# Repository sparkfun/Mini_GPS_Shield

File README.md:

# Pro_Mini_GPS_Shield
A GPS Shield for the Arduino Pro Mini

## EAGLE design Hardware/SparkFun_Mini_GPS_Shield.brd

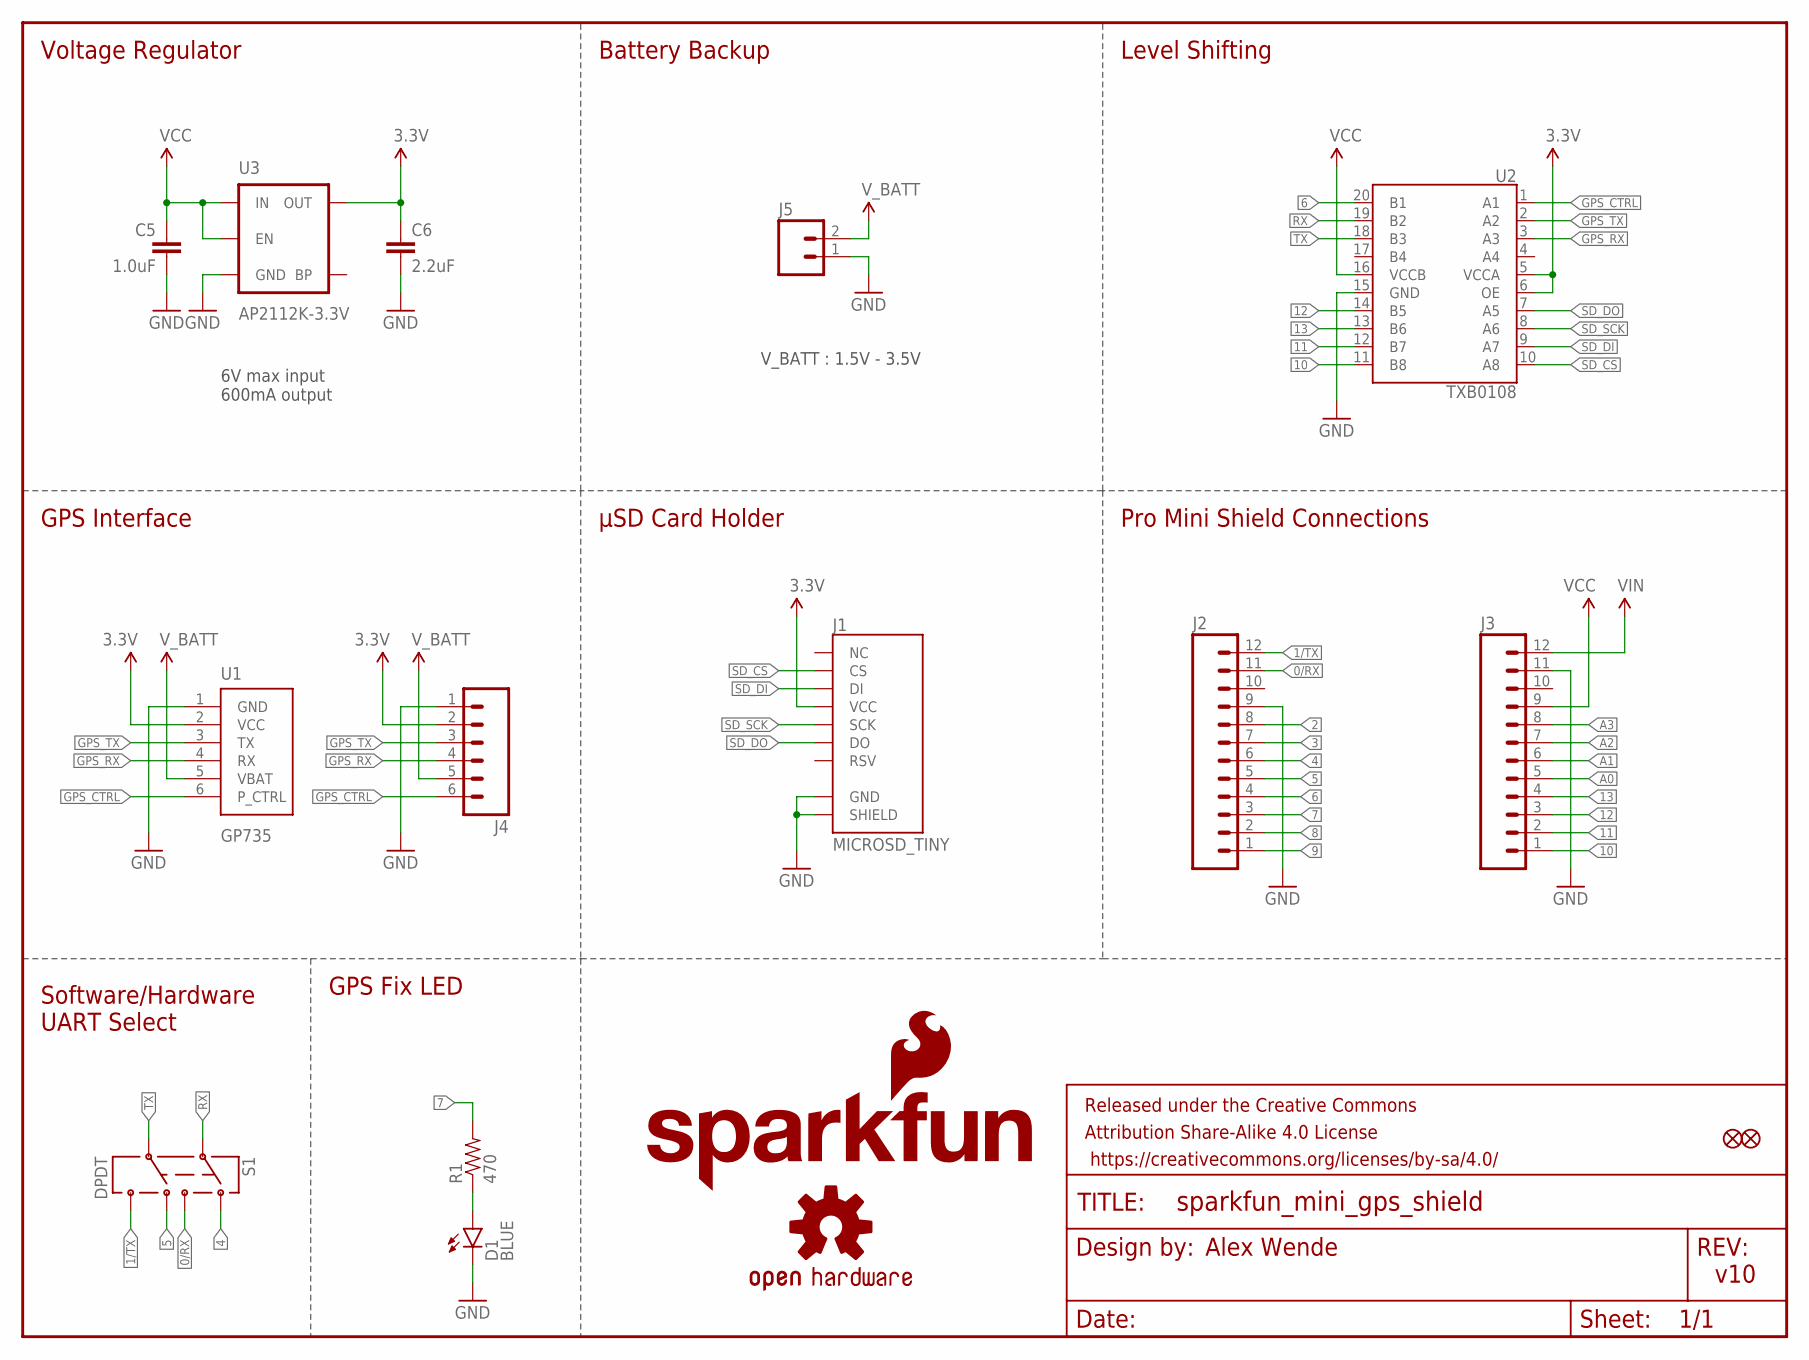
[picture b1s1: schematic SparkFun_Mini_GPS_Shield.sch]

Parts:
C5: 1.0uF; 0805-CAP
C6: 2.2uF; 0603-CAP
D1: BLUE; LED-0603
FD1, FD2: FIDUCIALUFIDUCIAL; MICRO-FIDUCIAL
FRAME1: FRAME-LETTER; CREATIVE_COMMONS
J1: MICROSD_TINY
J2, J3: M12NO_SILK; 1X12_NO_SILK
J4: M06NO_SILK_FEMALE_PTH; 1X06_NO_SILK
J5: M021X02_NO_SILK; 1X02_NO_SILK
LOGO1: OSHW-LOGOS; OSHW-LOGO-S
LOGO3: SFE_LOGO_FLAME.1_INCH; SFE_LOGO_FLAME_.1
LOGO4: SFE_LOGO_NAME.1_INCH; SFE_LOGO_NAME_.1
R1: 470; 0603-RES
S1: DPDT; AYZ0202
U1: GP735
U2: TXB0108; UFDFN-20
U3: AP2112K-3.3V; SOT23-5

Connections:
0/RX: J2.11, S1.3
1/TX: J2.12, S1.6
2: J2.8
3: J2.7
3.3V: C6.1, J1.4 (VCC), J4.2, U1.2 (VCC), U2.5 (VCCA), U2.6 (OE), U3.5 (OUT)
4: J2.6, S1.1
5: J2.5, S1.4
6: J2.4, U2.20 (B1)
7: J2.3, R1.2
8: J2.2
9: J2.1
10: J3.1, U2.11 (B8)
11: J3.2, U2.12 (B7)
12: J3.3, U2.14 (B5)
13: J3.4, U2.13 (B6)
A0: J3.5
A1: J3.6
A2: J3.7
A3: J3.8
GND: C5.2, C6.2, D1.C, J1.6 (GND), J1.GND1 (SHIELD), J1.GND2 (SHIELD), J1.GND3 (SHIELD), J1.GND4 (SHIELD), J1.GND5 (SHIELD), J1.GND6 (SHIELD), J2.9, J3.11, J4.1, J5.1, U1.1 (GND), U2.15 (GND), U3.2 (GND)
GPS_CTRL: J4.6, U1.6 (P_CTRL), U2.1 (A1)
GPS_RX: J4.4, U1.4 (RX), U2.3 (A3)
GPS_TX: J4.3, U1.3 (TX), U2.2 (A2)
unnamed: D1.A, R1.1
RX: S1.2, U2.19 (B2)
SD_CS: J1.2 (CS), U2.10 (A8)
SD_DI: J1.3 (DI), U2.9 (A7)
SD_DO: J1.7 (DO), U2.7 (A5)
SD_SCK: J1.5 (SCK), U2.8 (A6)
TX: S1.5, U2.18 (B3)
VCC: C5.1, J3.9, U2.16 (VCCB), U3.1 (IN), U3.3 (EN)
VIN: J3.12
V_BATT: J4.5, J5.2, U1.5 (VBAT)

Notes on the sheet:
6V max input 600mA output
Voltage Regulator
Battery Backup
Level Shifting
GPS Interface
Pro Mini Shield Connections
μSD Card Holder
Software/Hardware UART Select
GPS Fix LED
Alex Wende
v10
V_BATT : 1.5V - 3.5V

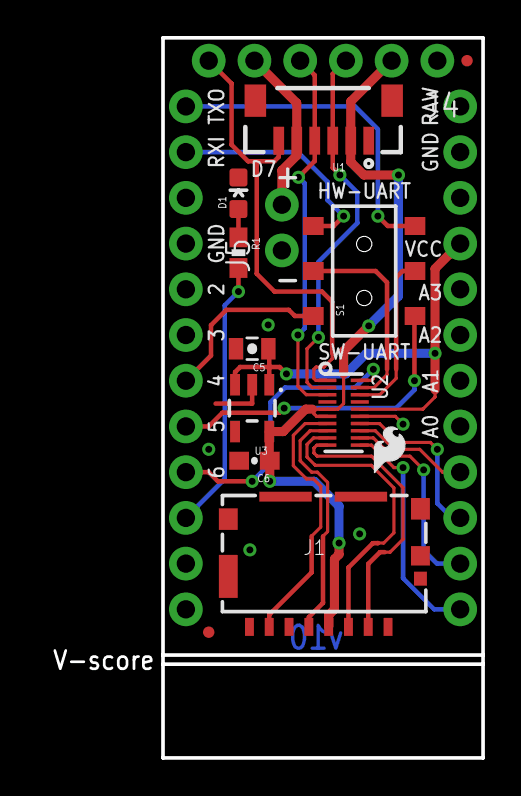
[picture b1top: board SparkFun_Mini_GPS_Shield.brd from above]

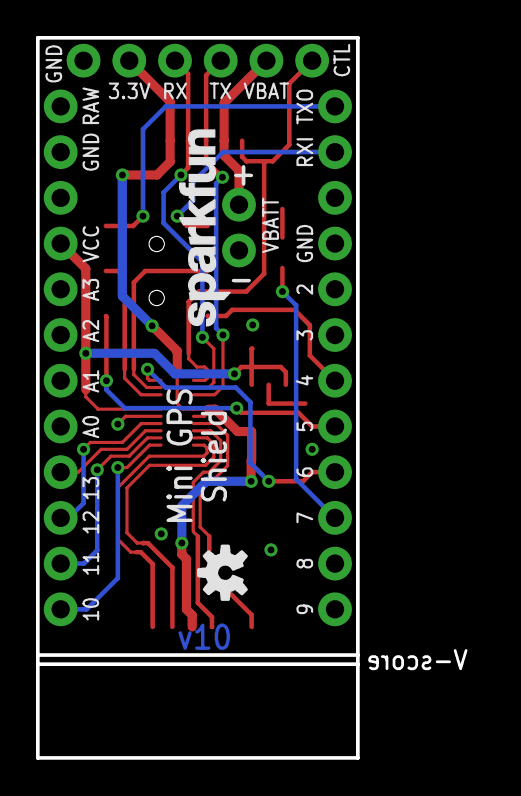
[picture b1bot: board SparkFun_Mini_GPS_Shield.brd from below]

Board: 2 copper layers, 24.7 x 40.0 mm, 19 parts (2 on the bottom side), 24 nets.

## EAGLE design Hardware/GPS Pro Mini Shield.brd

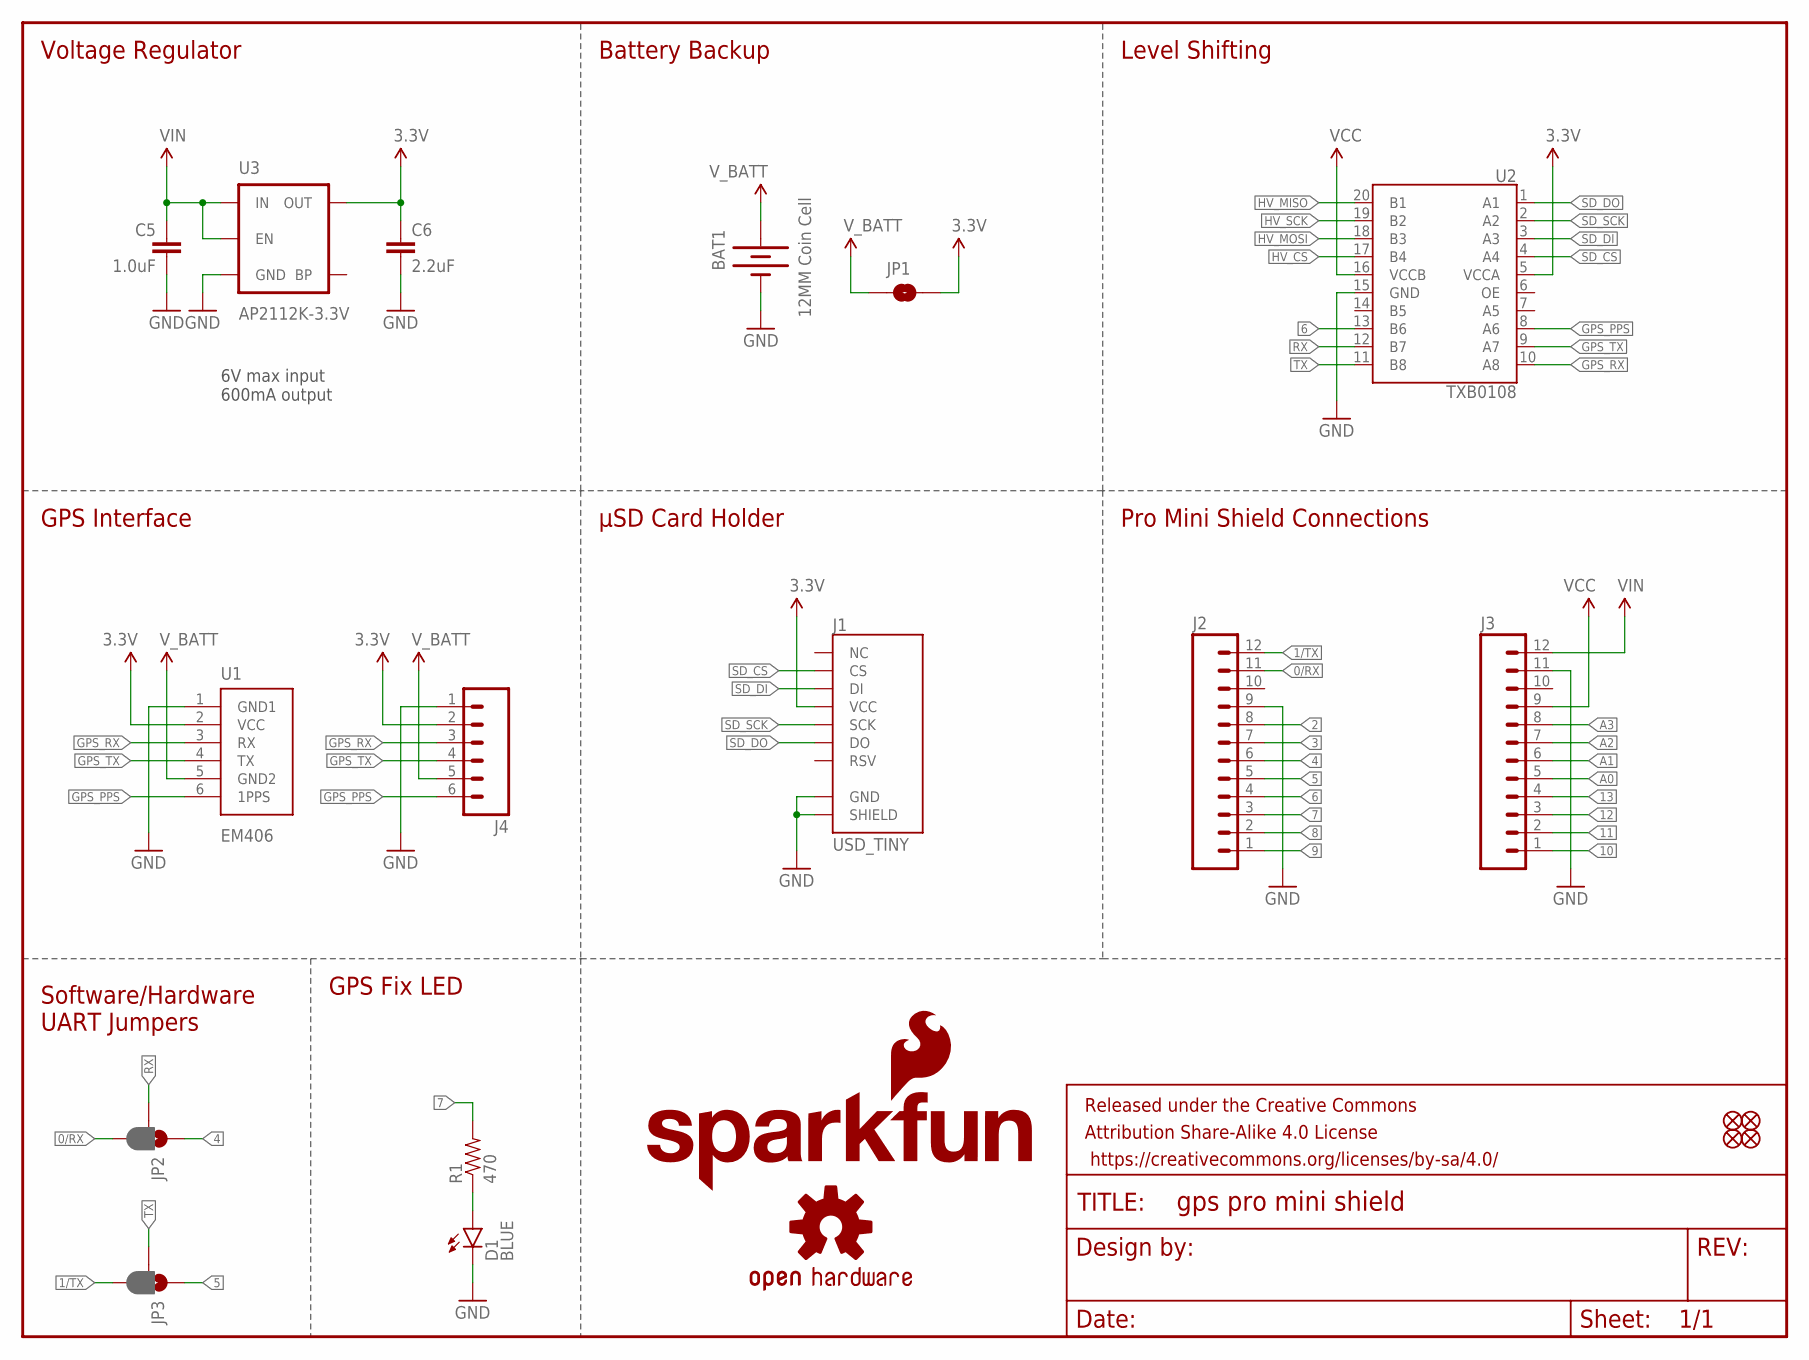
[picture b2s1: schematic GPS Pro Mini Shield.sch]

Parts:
BAT1: 12MM Coin Cell; BATTCON_12MM
C5: 1.0uF; 0805-CAP
C6: 2.2uF; 0603-CAP
D1: BLUE; LED-0603
FD1, FD2, FD3, FD4: FIDUCIALUFIDUCIAL; MICRO-FIDUCIAL
FRAME1: FRAME-LETTER; CREATIVE_COMMONS
J1: USD_TINY; SLIM_USD
J2, J3: M12NO_SILK; 1X12_NO_SILK
J4: M06NO_SILK_FEMALE_PTH; 1X06_NO_SILK
JP1: JUMPER-PAD-2-NOYES_SILK; PAD-JUMPER-2-NO_YES_SILK
JP2, JP3: JUMPER-PAD-3-2OF3_NC_BY_PASTE; PAD-JUMPER-3-2OF3_NC_BY_PASTE_YES_SILK_FULL_BOX
LOGO1: OSHW-LOGOS; OSHW-LOGO-S
LOGO3: SFE_LOGO_FLAME.1_INCH; SFE_LOGO_FLAME_.1
LOGO4: SFE_LOGO_NAME.1_INCH; SFE_LOGO_NAME_.1
R1: 470; 0603-RES
U1: EM406
U2: TXB0108; UFDFN-20
U3: AP2112K-3.3V; SOT23-5

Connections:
0/RX: J2.11, JP2.3
1/TX: J2.12, JP3.3
2: J2.8
3: J2.7
3.3V: C6.1, J1.4 (VCC), J4.2, JP1.2, U1.2 (VCC), U2.5 (VCCA), U3.5 (OUT)
4: J2.6, JP2.1
5: J2.5, JP3.1
6: J2.4, U2.13 (B6)
7: J2.3, R1.2
8: J2.2
9: J2.1
10: J3.1
11: J3.2
12: J3.3
13: J3.4
A0: J3.5
A1: J3.6
A2: J3.7
A3: J3.8
GND: BAT1.GND (-), C5.2, C6.2, D1.C, J1.6 (GND), J1.GND1 (SHIELD), J1.GND2 (SHIELD), J1.GND3 (SHIELD), J1.GND4 (SHIELD), J1.GND5 (SHIELD), J1.GND6 (SHIELD), J2.9, J3.11, J4.1, U1.1 (GND1), U2.15 (GND), U3.2 (GND)
GPS_PPS: J4.6, U1.6 (1PPS), U2.8 (A6)
GPS_RX: J4.3, U1.3 (RX), U2.10 (A8)
GPS_TX: J4.4, U1.4 (TX), U2.9 (A7)
HV_CS: U2.17 (B4)
HV_MISO: U2.20 (B1)
HV_MOSI: U2.18 (B3)
HV_SCK: U2.19 (B2)
unnamed: D1.A, R1.1
RX: JP2.2, U2.12 (B7)
SD_CS: J1.2 (CS), U2.4 (A4)
SD_DI: J1.3 (DI), U2.3 (A3)
SD_DO: J1.7 (DO), U2.1 (A1)
SD_SCK: J1.5 (SCK), U2.2 (A2)
TX: JP3.2, U2.11 (B8)
VCC: J3.9, U2.16 (VCCB)
VIN: C5.1, J3.12, U3.1 (IN), U3.3 (EN)
V_BATT: BAT1.PWR@1 (+), J4.5, JP1.1, U1.5 (GND2)

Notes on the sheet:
6V max input 600mA output
Voltage Regulator
Battery Backup
Level Shifting
GPS Interface
Pro Mini Shield Connections
μSD Card Holder
Software/Hardware UART Jumpers
GPS Fix LED

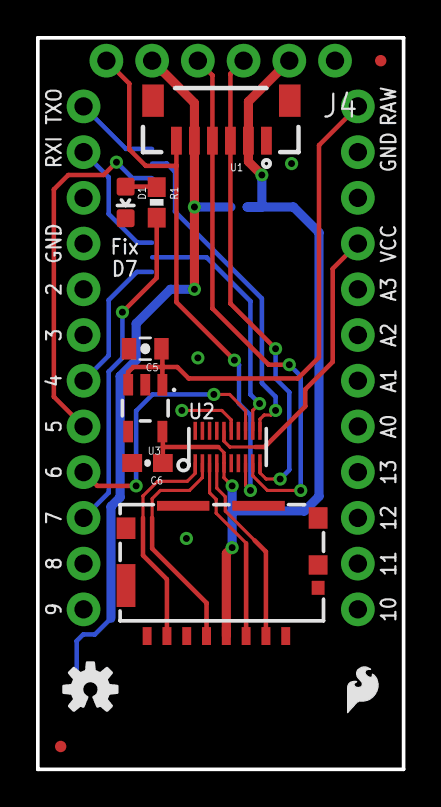
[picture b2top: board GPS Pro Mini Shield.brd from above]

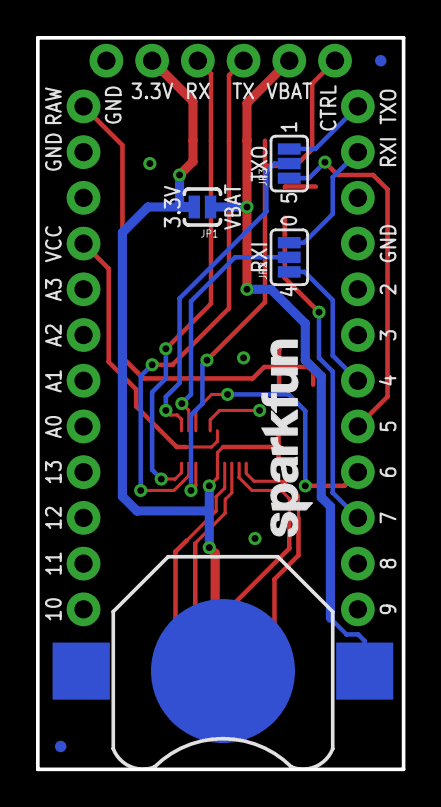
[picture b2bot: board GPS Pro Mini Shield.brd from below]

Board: 2 copper layers, 20.3 x 40.6 mm, 23 parts (7 on the bottom side), 21 nets.

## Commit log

2016-08-29 Initial Commit
    Added Eagle files and uSD card holder library
2016-08-30 Update file names and library
    - Updated file names to follow standard
    - Updated library with PROD_ID numbers
2016-08-30 Updated GPS label
    Changed from GPS_PPS to GPS_CTRL
2016-08-30 Added board designer name and version number
2016-09-01 Design Review Changes
    - Fixed SPI traces
    - Moved VIN of regulator to VIN instead of RAW
    - Removed jumpers for software/hardware uart with DPDT switch
    - Added product name to board
    - Replaced coin cell battery with two PTH pins to make the board smaller
2016-09-06 QC Changes
    - shorted output enable to VCCA
    - added note of PCB thickness to tDocu
    - added VBATT to bottom silk for 2-pin vbatt header
2016-09-06 QC changes
    -shorted output enable to VCCA
    - added note about PCB thickness
    - added VBATT to bottom silk for 2-pin vbatt header
2016-09-06 Adding .gitignore
2016-09-06 Minor changes
2016-10-05 V10 Changes
    - Changed board name to "Mini GPS Shield".
    - Extended board length to better support uSD card.
    - Added v-score to board extention
    - Changed control pin name to "CTL" instead of "CTR"
2016-10-05 Moved v-score label
    - Moved v-score label to dimention layer instead of tDocu
2016-10-07 Changed UART net labels
    0/RX and 1/TX are now RX/0 and TX/1
2016-12-02 Updated README
    Added product photo and updated text

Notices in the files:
parts and their libraries:
SparkFun-Connectors: Licensing: Creative Commons ShareAlike 4.0 International - https://creativecommons.org/licenses/by-sa/4.0
SparkFun-Aesthetics: Released under the Creative Commons Attribution Share-Alike 4.0 License
SparkFun-Aesthetics: https://creativecommons.org/licenses/by-sa/4.0
